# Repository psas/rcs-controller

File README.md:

# RCS Controller (Hardware and Firmware)
The controller PCB for the RCS v2 module

Design documentation can be found [here](https://docs.google.com/document/d/1iXMG_Qmra7nCvFc8n4LBztUYELcxyuHCIxhkm7w4VaU/edit?usp=sharing).

## LICENSE

Copyright the Portland State Aerospace Society, 2025.

This source describes Open Hardware that is licensed under CERN-OHL-S v2, or any later version.

You may redistribute and modify this source and make products using it under the terms of the CERN-OHL-S v2 (https://ohwr.org/cern_ohl_s_v2.txt).

This source is distributed WITHOUT ANY EXPRESS OR IMPLIED WARRANTY, INCLUDING OF MERCHANTABILITY, SATISFACTORY QUALITY AND FITNESS FOR A PARTICULAR PURPOSE. Please see the CERN-OHL-S v2 for applicable conditions.

Source location: https://github.com/psas/

If you require a different license for this open hardware project, please contact us at [aerospace@pdx.edu](mailto:aerospace@pdx.edu).

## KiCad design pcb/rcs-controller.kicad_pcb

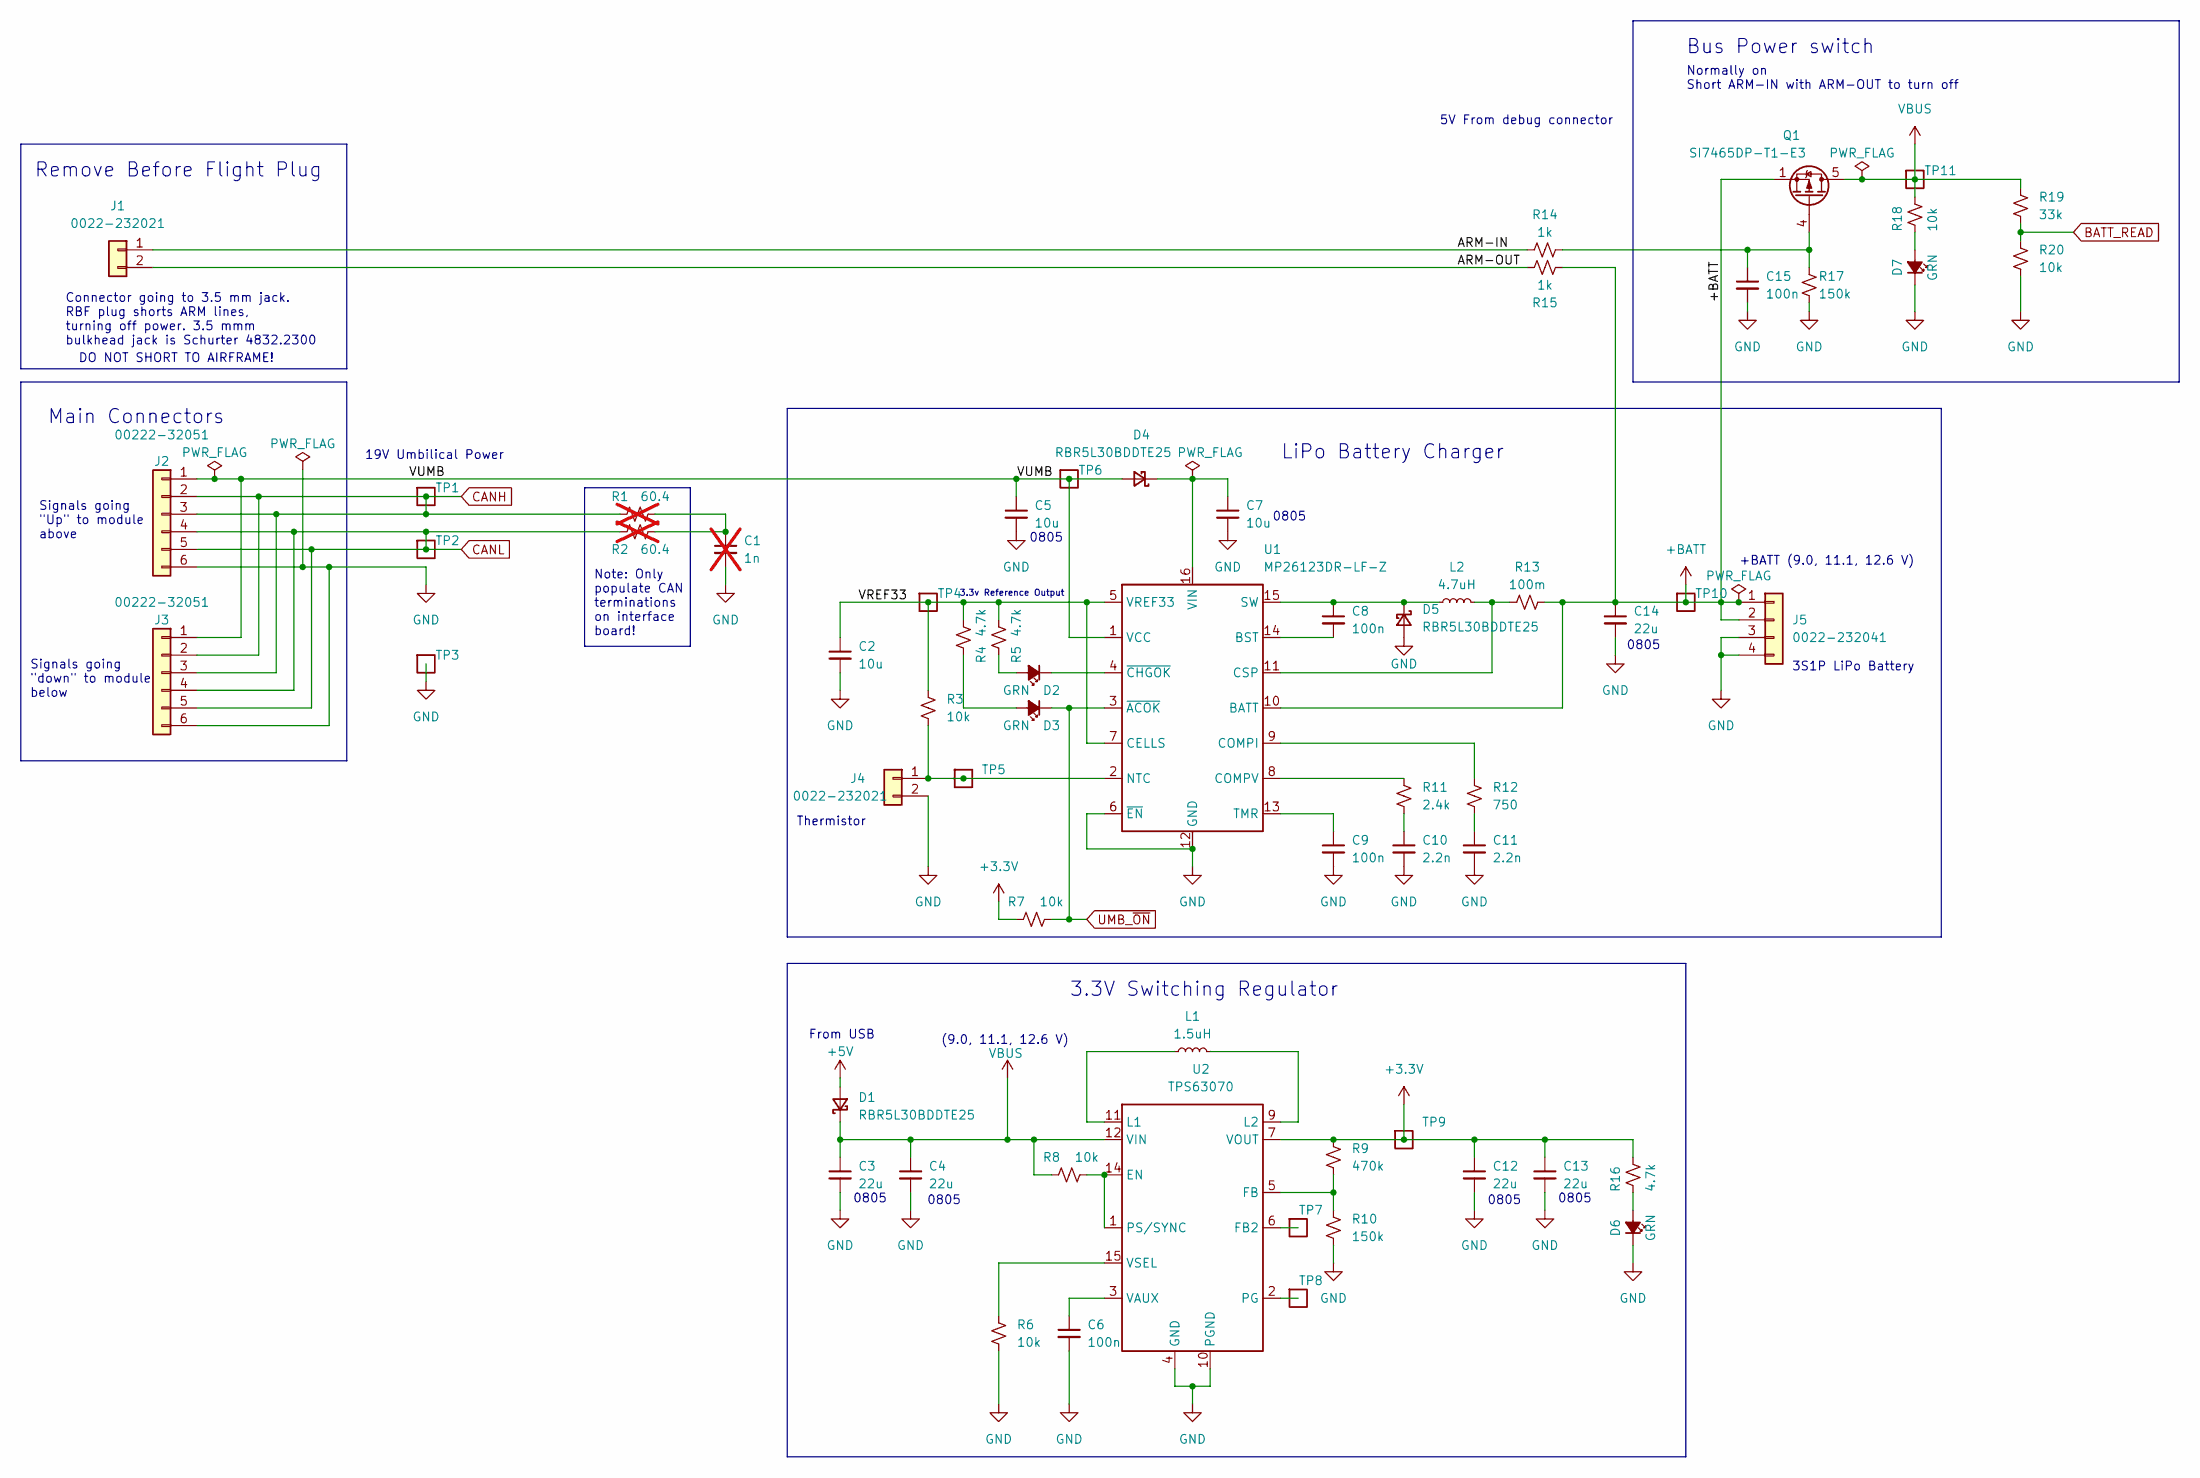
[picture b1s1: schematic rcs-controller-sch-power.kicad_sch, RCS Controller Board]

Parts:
C1: 1n; C_0603_1608Metric; MPN CL10B102KB85PNL; not fitted
C2, C5, C7: 10u; C_0805_2012Metric; MPN GRM21BR61H106KE43L
C3, C4, C12, C13, C14: 22u; C_0805_2012Metric; MPN C2012X5R1V226M125AC
C6, C8, C9, C15: 100n; C_0603_1608Metric; MPN CL10B104KB8WPNC
C10, C11: 2.2n; C_0603_1608Metric; MPN CL10B222KB8WPNC
D1, D4, D5: RBR5L30BDDTE25; D_SMA; MPN RBR5L30BDDTE25
D2, D3, D6, D7: GRN; LED_0603_1608Metric; MPN 150060GS75000
J1, J4: 0022-232021; Molex_KK-254_AE-6410-02A_1x02_P2.54mm_Vertical; MPN 22232021
J2, J3: 00222-32051; Molex_KK-254_AE-6410-06A_1x06_P2.54mm_Vertical; MPN 22232061
J5: 0022-232041; Molex_KK-254_AE-6410-04A_1x04_P2.54mm_Vertical; MPN 22232041
L1: 1.5uH; L_Vishay_IHLP-2020; MPN IHLP2020CZER1R5M11
L2: 4.7uH; L_Vishay_IHLP-2020; MPN IHLP2020BZER4R7M11
Q1: SI7465DP-T1-E3; PowerPAK_SO-8_Single; MPN SI7141DP-T1-GE3
R1, R2: 60.4; R_1206_3216Metric; MPN RC0603FR-0760R4L; not fitted
R3, R6, R7, R8, R18, R20: 10k; R_0603_1608Metric; MPN RC0603FR-0710KL
R4, R5, R16: 4.7k; R_0603_1608Metric; MPN RC0603FR-074K7L
R9: 470k; R_0603_1608Metric; MPN RC0603FR-07470KL
R10, R17: 150k; R_0603_1608Metric; MPN RC0603FR-07150KL
R11: 2.4k; R_0603_1608Metric; MPN RC0603FR-072K4L
R12: 750; R_0603_1608Metric; MPN RC0603FR-07750RL
R13: 100m; R_1206_3216Metric; MPN CSR1206FTR100
R14, R15: 1k; R_0603_1608Metric; MPN RC0603FR-071KL
R19: 33k; R_0603_1608Metric; MPN RC0603FR-0733KL
TP1, TP2, TP3, TP4, TP5, TP6, TP7, TP8, TP9, TP10, TP11: Test-Point; TP-through-hole-1X01
U1: MP26123DR-LF-Z; QFN-16-1EP_4x4mm_P0.65mm_EP2.5x2.5mm; MPN MP26123DR-LF-Z
U2: TPS63070; U-TI-TPS63070; MPN TPS63070RNMR

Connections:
+3.3V: C12.1, C13.1, R7.1, R9.1, R16.1, TP9.1, U2.7 (VOUT), U2.8 (VOUT), U2.TIE2 (VOUT); also elsewhere on the board
+5V: D1.2 (A); also elsewhere on the board
+BATT: C14.1, J5.1, J5.2, Q1.1 (S), Q1.2 (S), Q1.3 (S), R13.2, R15.1, TP10.1, U1.10 (BATT)
/Power/ARM-IN: J1.1, R14.1
/Power/ARM-OUT: J1.2, R15.2
/Power/VREF33: C2.1, R3.1, R4.1, R5.1, TP4.1, U1.5 (VREF33), U1.7 (CELLS)
/Power/VUMB: C5.1, D4.2 (A), J2.1, J3.1, TP6.1, U1.1 (VCC)
BATT_READ: R19.2, R20.1; also elsewhere on the board
CANH: J2.2, J2.3, J3.2, J3.3, R1.1, TP1.1
CANL: J2.4, J2.5, J3.4, J3.5, R2.2, TP2.1
GND: C1.2, C2.2, C3.2, C4.2, C5.2, C6.2, C7.2, C9.2, C10.2, C11.2, C12.2, C13.2, C14.2, C15.2, D5.2 (A), D6.1 (K), D7.1 (K), J2.6, J3.6, J4.2, J5.3, J5.4, R6.2, R10.2, R17.2, R20.2, TP3.1, U1.6 (~EN), U1.12 (GND), U1.17 (GND), U2.4 (GND), U2.10 (PGND); also elsewhere on the board
unnamed: C1.1, R1.2, R2.1
unnamed: C10.1, R11.2
unnamed: C11.1, R12.2
unnamed: D2.2 (A), R5.2
unnamed: D2.1 (K), U1.4 (~CHGOK)
unnamed: D3.2 (A), R4.2
unnamed: C7.1, D4.1 (K), U1.16 (VIN)
unnamed: C8.1, D5.1 (K), L2.1, U1.15 (SW)
unnamed: D6.2 (A), R16.2
unnamed: D7.2 (A), R18.2
unnamed: J4.1, R3.2, TP5.1, U1.2 (NTC)
unnamed: C15.1, Q1.4 (G), R14.2, R17.1
unnamed: C8.2, U1.14 (BST)
unnamed: R12.1, U1.9 (COMPI)
unnamed: R11.1, U1.8 (COMPV)
unnamed: L2.2, R13.1, U1.11 (CSP)
unnamed: C9.1, U1.13 (TMR)
unnamed: R8.2, U2.1 (PS/SYNC), U2.14 (EN)
unnamed: TP7.1, U2.6 (FB2)
unnamed: R9.2, R10.1, U2.5 (FB)
unnamed: L1.1, U2.11 (L1)
unnamed: L1.2, U2.9 (L2)
unnamed: TP8.1, U2.2 (PG)
unnamed: C6.1, U2.3 (VAUX)
unnamed: R6.1, U2.15 (VSEL)
UMB_~ON: D3.1 (K), R7.2, U1.3 (~ACOK); also elsewhere on the board
VBUS: C3.1, C4.1, D1.1 (K), Q1.5 (D), R8.1, R18.1, R19.1, TP11.1, U2.12 (VIN), U2.13 (VIN), U2.TIE1 (VIN); also elsewhere on the board

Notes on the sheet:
LiPo Battery Charger
From USB
0805
DO NOT SHORT TO AIRFRAME!
Thermistor
Signals going "down" to module below
Normally on Short ARM-IN with ARM-OUT to turn off
Connector going to 3.5 mm jack. RBF plug shorts ARM lines, turning off power. 3.5 mmm bulkhead jack is Schurter 4832.2300
Note: Only populate CAN terminations on interface board!
3S1P LiPo Battery
Signals going "Up" to module above
19V Umbilical Power
(9.0, 11.1, 12.6 V)
+BATT (9.0, 11.1, 12.6 V)
Bus Power switch
Main Connectors
3.3V Switching Regulator
5V From debug connector
3.3v Reference Output
Remove Before Flight Plug

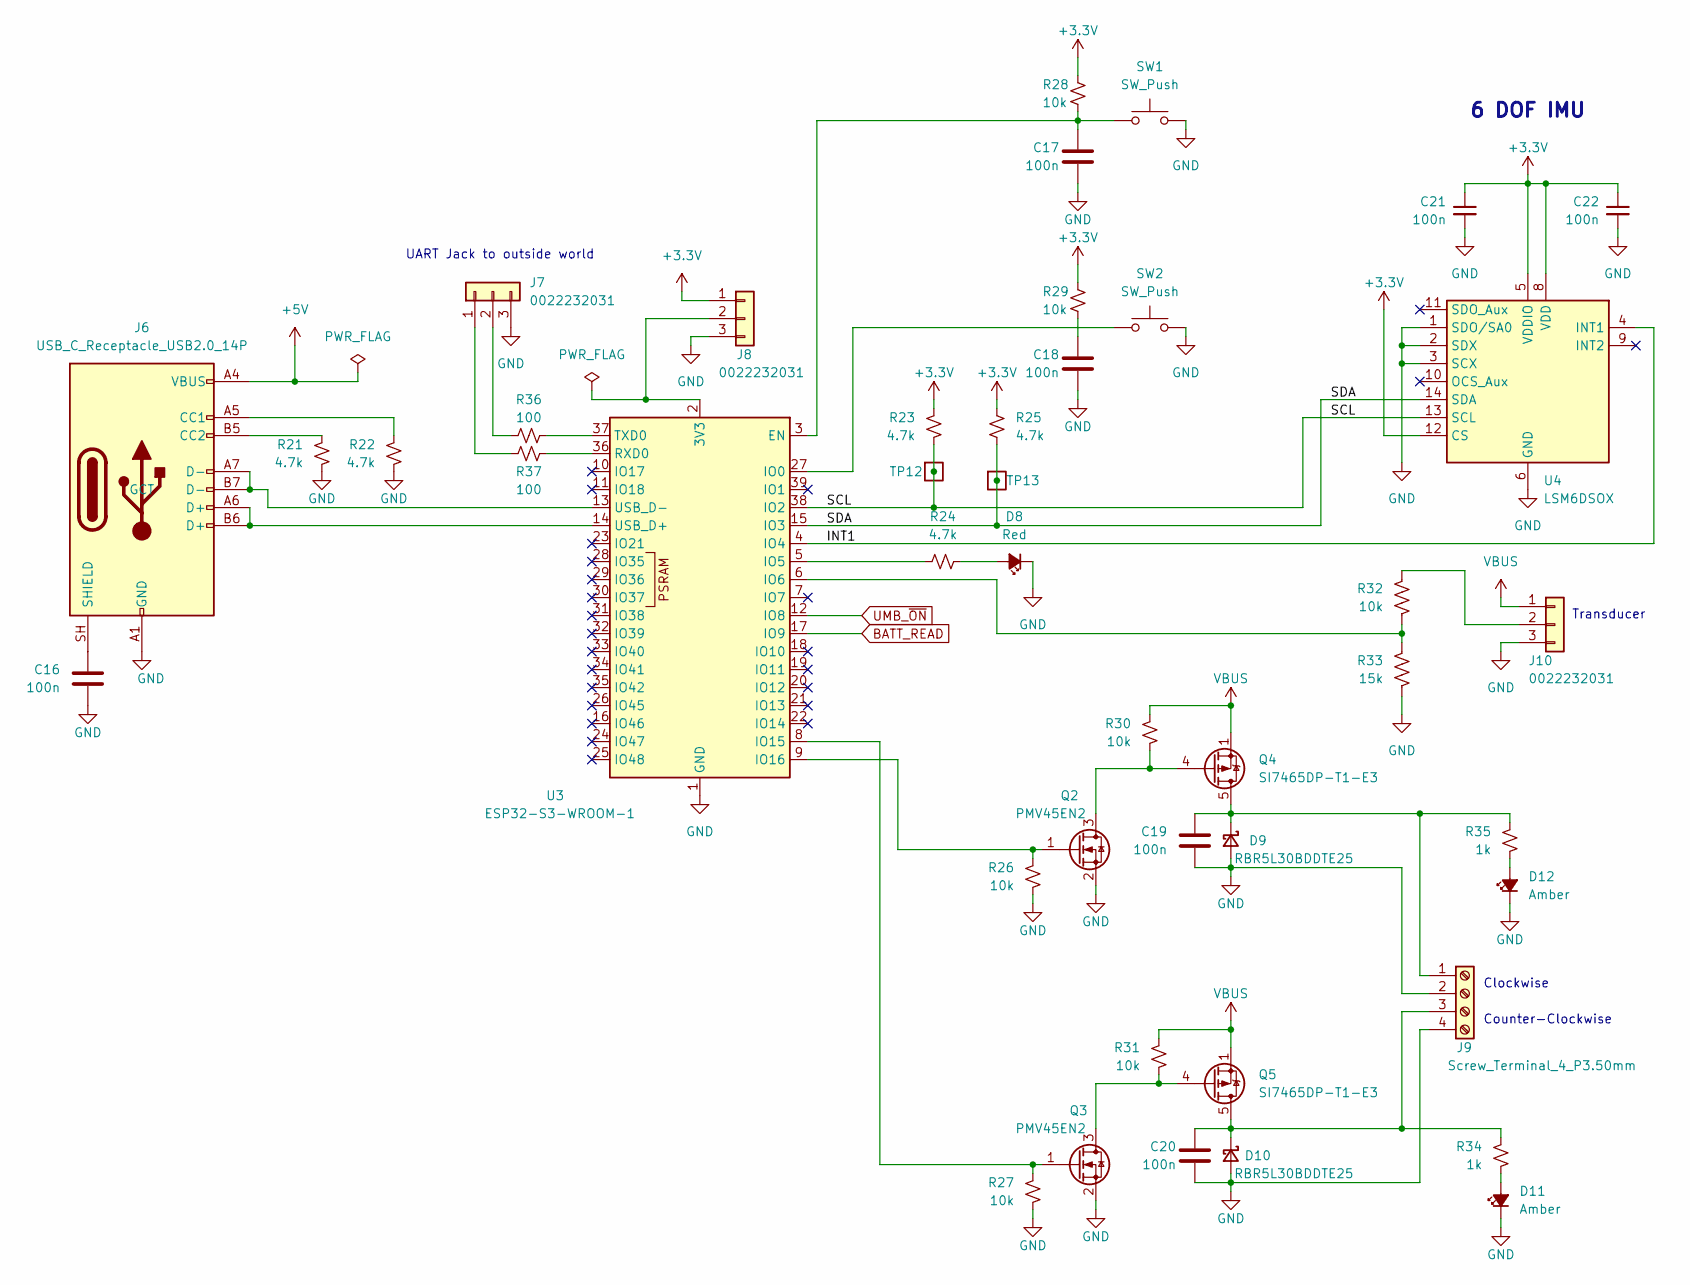
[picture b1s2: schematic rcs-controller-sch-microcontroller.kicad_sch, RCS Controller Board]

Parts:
C16, C17, C18, C19, C20, C21, C22: 100n; C_0603_1608Metric; MPN CL10B104KB8WPNC
D8: Red; LED_0603_1608Metric; MPN 150060SS75000
D9, D10: RBR5L30BDDTE25; D_SMA; MPN RBR5L30BDDTE25
D11, D12: Amber; LED_0603_1608Metric; MPN 150060YS75000
J6: USB_C_Receptacle_USB2.0_14P; USB_C_Receptacle_Palconn_UTC16-G; MPN USB4105-GF-A
J7, J8, J10: 0022232031; Molex_KK-254_AE-6410-03A_1x03_P2.54mm_Vertical; MPN 22232031
J9: Screw_Terminal_4_P3.50mm; TerminalBlock_Phoenix_PT-1,5-4-3.5-H_1x04_P3.50mm_Horizontal; MPN 1751264
Q2, Q3: PMV45EN2; SOT-23-3; MPN PMV45EN2R
Q4, Q5: SI7465DP-T1-E3; PowerPAK_SO-8_Single; MPN SI7141DP-T1-GE3
R21, R22, R23, R24, R25: 4.7k; R_0603_1608Metric; MPN RC0603FR-074K7L
R26, R27, R28, R29, R30, R31, R32: 10k; R_0603_1608Metric; MPN RC0603FR-0710KL
R33: 15k; R_0603_1608Metric; MPN RC0603JR-0715KL
R34, R35: 1k; R_0603_1608Metric; MPN RC0603FR-071KL
R36, R37: 100; R_0603_1608Metric
SW1, SW2: SW_Push; SW_PUSH_6mm; MPN B3F-1000
TP12, TP13: Test-Point; TP-through-hole-1X01
U3: ESP32-S3-WROOM-1; MPN ESP32-S3-WROOM-1-N4R8
U4: LSM6DSOX; LGA-14_3x2.5mm_P0.5mm_LayoutBorder3x4y; MPN LSM6DSOXTR

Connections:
+3.3V: C21.1, C22.1, J8.1, R23.1, R25.1, R28.1, R29.1, U4.5 (VDDIO), U4.8 (VDD), U4.12 (CS); also elsewhere on the board
+5V: J6.A4 (VBUS), J6.A9 (VBUS), J6.B4 (VBUS), J6.B9 (VBUS); also elsewhere on the board
/Microcontroller/INT1: U3.4 (IO4), U4.4 (INT1)
/Microcontroller/SCL: R23.2, TP12.1, U3.38 (IO2), U4.13 (SCL)
/Microcontroller/SDA: R25.2, TP13.1, U3.15 (IO3), U4.14 (SDA)
BATT_READ: U3.17 (IO9); also elsewhere on the board
GND: C16.2, C17.2, C18.2, C19.2, C20.2, C21.2, C22.2, D8.1 (K), D9.2 (A), D10.2 (A), D11.1 (K), D12.1 (K), J6.A1 (GND), J6.A12 (GND), J6.B1 (GND), J6.B12 (GND), J7.3, J8.3, J9.2, J9.4, J10.3, Q2.2 (S), Q3.2 (S), R21.2, R22.2, R26.2, R27.2, R33.1, SW1.2, SW2.2, U3.1 (GND), U3.40 (GND), U3.41 (GND), U4.1 (SDO/SA0), U4.2 (SDX), U4.3 (SCX), U4.6 (GND), U4.7 (GND); also elsewhere on the board
unnamed: C18.1, R29.2
unnamed: D8.2 (A), R24.2
unnamed: C19.1, D9.1 (K), J9.1, Q4.5 (D), R35.1
unnamed: C20.1, D10.1 (K), J9.3, Q5.5 (D), R34.1
unnamed: D11.2 (A), R34.2
unnamed: D12.2 (A), R35.2
unnamed: J6.A5 (CC1), R22.1
unnamed: J6.B5 (CC2), R21.1
unnamed: C16.1, J6.SH (SHIELD)
unnamed: J7.1, R37.1, R37.2, U3.36 (RXD0)
unnamed: J7.2, R36.1, R36.2, U3.37 (TXD0)
unnamed: J8.2, U3.2 (3V3)
unnamed: J10.2, R32.1
unnamed: Q2.3 (D), Q4.4 (G), R30.2
unnamed: Q2.1 (G), R26.1, U3.9 (IO16)
unnamed: Q3.3 (D), Q5.4 (G), R31.2
unnamed: Q3.1 (G), R27.1, U3.8 (IO15)
unnamed: C17.1, R28.2, SW1.1, U3.3 (EN)
unnamed: SW2.1, U3.27 (IO0)
unnamed: R24.1, U3.5 (IO5)
unnamed: R32.2, R33.2, U3.6 (IO6)
unnamed: J6.A6 (D+), J6.B6 (D+), U3.14 (USB_D+)
unnamed: J6.A7 (D-), J6.B7 (D-), U3.13 (USB_D-)
UMB_~ON: U3.12 (IO8); also elsewhere on the board
VBUS: J10.1, Q4.1 (S), Q4.2 (S), Q4.3 (S), Q5.1 (S), Q5.2 (S), Q5.3 (S), R30.1, R31.1; also elsewhere on the board

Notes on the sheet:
Transducer
Counter-Clockwise
Clockwise
6 DOF IMU
UART Jack to outside world

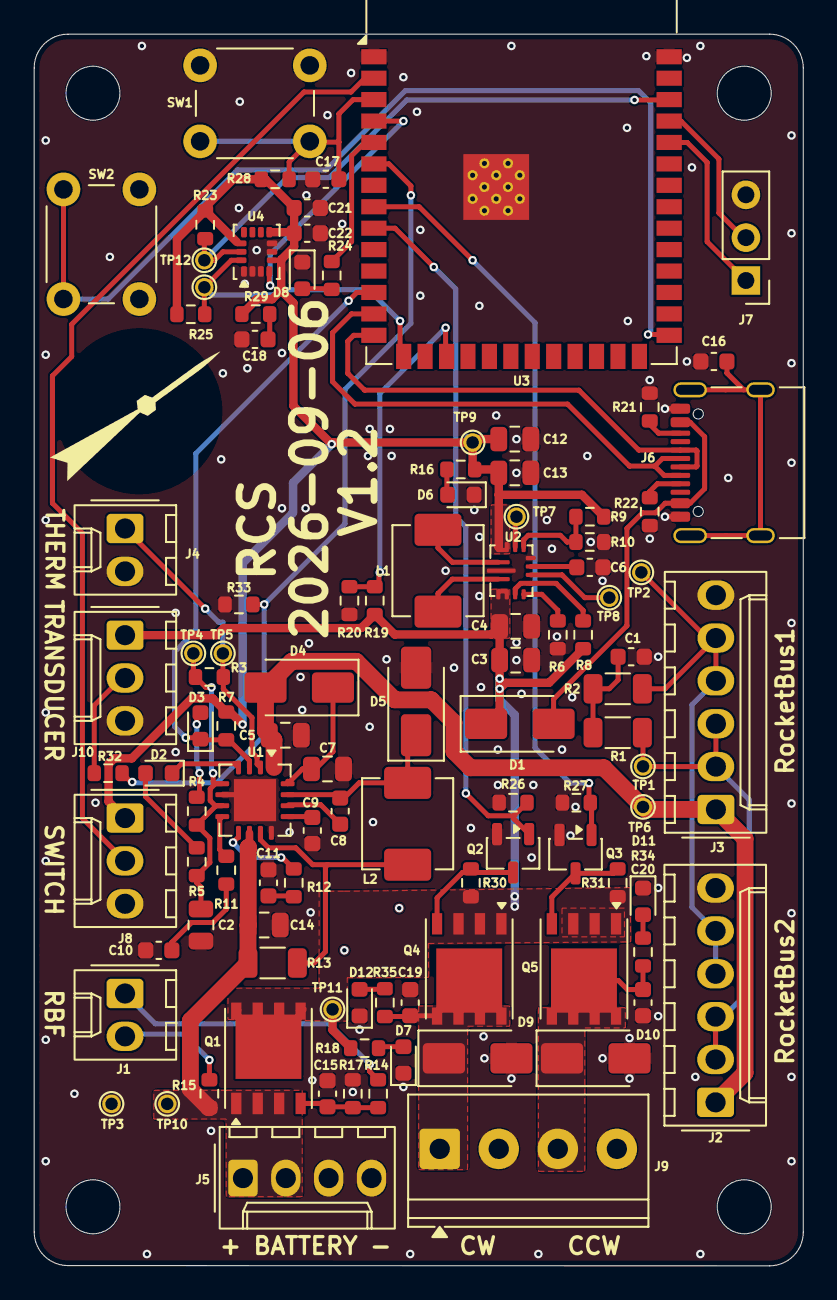
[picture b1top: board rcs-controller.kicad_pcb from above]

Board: 2 copper layers, 45.6 x 73.0 mm, 106 parts (0 on the bottom side), 64 nets.

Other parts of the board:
LOGO1: PSAS_LOGO_10X10

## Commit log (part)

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2025-07-17 Now with HTML BOM
2026-04-03 Initial commit of RCS test code
2026-04-16 added debug led and boot button
2026-04-18 Removed no connect flags to address warnings
2026-04-19 Potential switching circuit between battery and USB
2026-04-24 Updated gitignore for kicad 10
2026-04-24 power OR cleanup with Thomas for USB power
2026-04-24 Added Andrew's new power switching diode and removed some unconnected traces
2026-06-27 Added ports to transducer and power switch
2026-06-27 Added voltage divider for transducer and fixed connector identifier issue
